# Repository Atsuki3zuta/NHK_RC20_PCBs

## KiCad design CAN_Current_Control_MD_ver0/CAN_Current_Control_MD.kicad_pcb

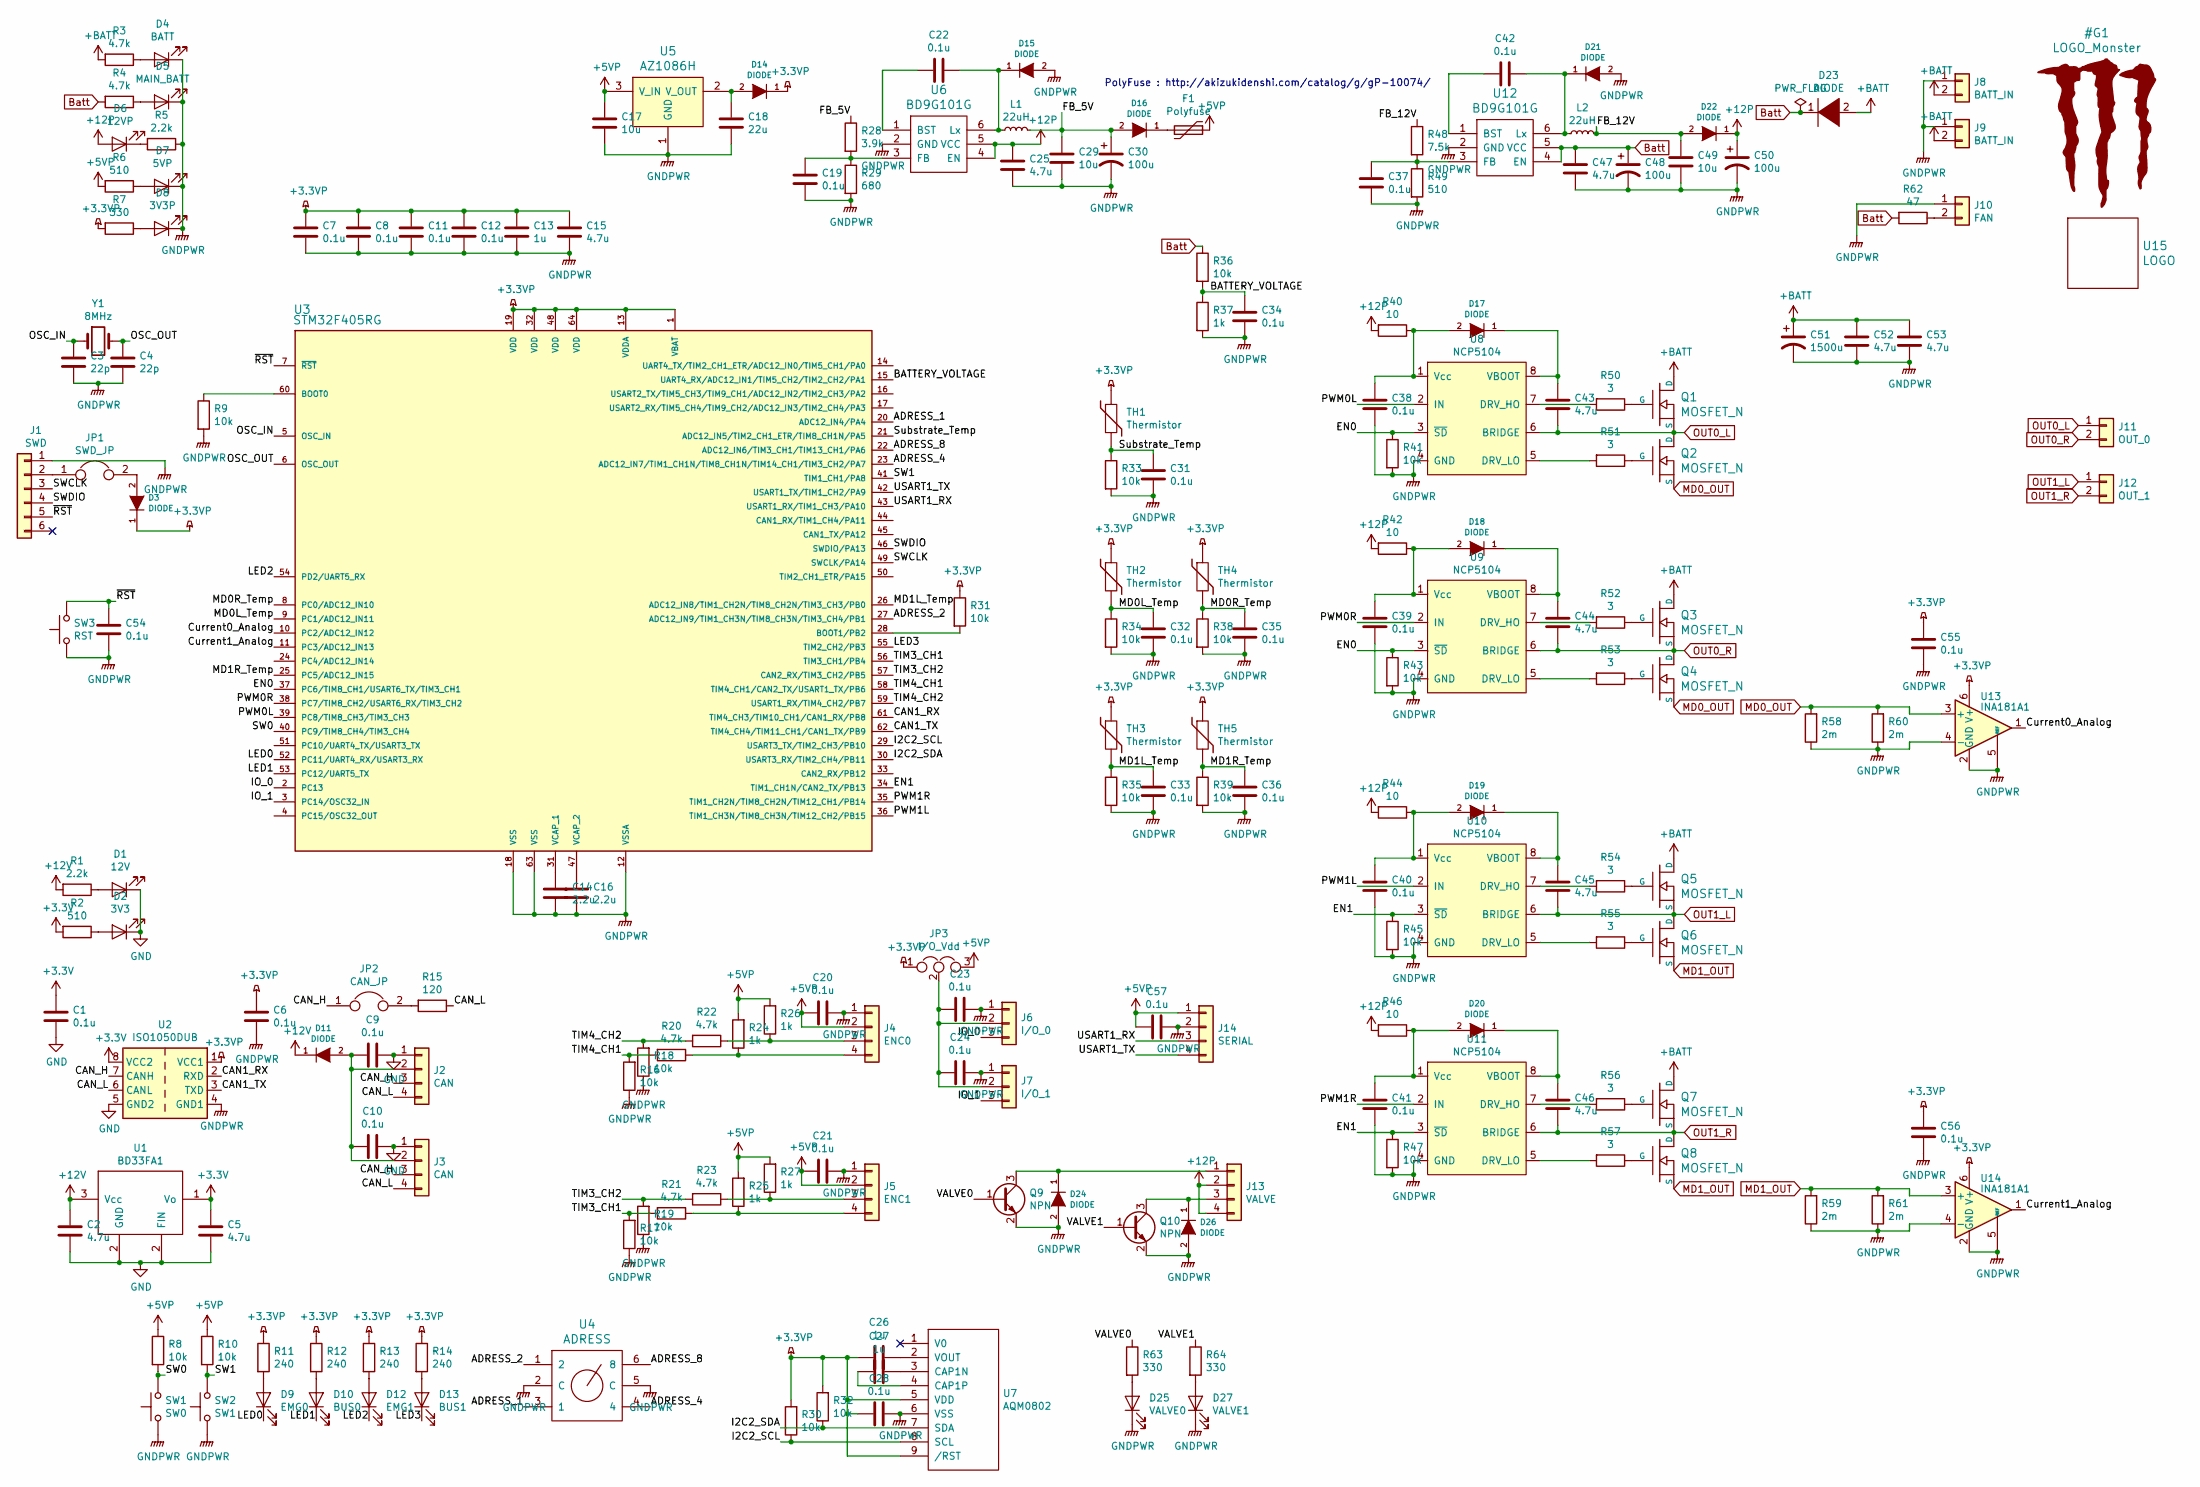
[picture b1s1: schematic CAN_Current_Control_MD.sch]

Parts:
C1, C8, C11, C12, C19, C20, C21, C22, C23, C24, C28, C31, C32, C33, C34, C35, C36, C38, C39, C40, C41, C42, C55, C56, C57: 0.1u; 1608_WP
C2, C5, C25, C43, C44, C45, C46, C47, C52, C53: 4.7u; C_0805_2012Metric
C3, C4: 22p; 1608_WP
C6, C7, C9, C10, C37, C54: 0.1u; C_0603_1608Metric
C13, C26, C27: 1u; 1608_WP
C14, C16: 2.2u; 1608_WP
C15: 4.7u; 1608_WP
C17: 10u; 1608_WP
C18: 22u; 1608_WP
C29, C49: 10u; C_0805_2012Metric
C30, C48, C50: 100u; CP_Radial_D5.0mm_P2.50mm
C51: 1500u; C_Radial_D13mm_H25.0mm_P5.00mm
D1: 12V; 1608_WP
D2: 3V3; 1608_WP
D3, D11, D14, D15, D16, D17, D18, D19, D20, D21, D22, D24, D26: DIODE; D_SOD-123
D4: BATT; LED_0603_1608Metric
D5: MAIN_BATT; LED_0603_1608Metric
D6: 12VP; LED_0603_1608Metric
D7: 5VP; LED_0603_1608Metric
D8: 3V3P; LED_0603_1608Metric
D9: EMG0; 1608_WP
D10: BUS0; 1608_WP
D12: EMG1; 1608_WP
D13: BUS1; 1608_WP
D23: DIODE; D_SMA
D25: VALVE0; LED_0603_1608Metric
D27: VALVE1; LED_0603_1608Metric
F1: Polyfuse; Fuse_1812_4532Metric_Pad1.30x3.40mm_HandSolder
J1: SWD; ZH_6P
J2, J3: CAN; XA_4L
J4: ENC0; XA_4L
J5: ENC1; XA_4L
J6: I/O_0; XA_3L
J7: I/O_1; XA_3L
J8: BATT_IN; XT60_F
J9: BATT_IN; XT60_M
J10: FAN; XA_2P
J11: OUT_0; XT60_F
J12: OUT_1; XT60_F
J13: VALVE; XA_4L
J14: SERIAL; PinSocket_1x04_P2.54mm_Vertical
JP1: SWD_JP; SolderJumper-2_P1.3mm_Open_TrianglePad1.0x1.5mm
JP2: CAN_JP; PinHeader_1x02_P2.54mm_Vertical
JP3: I/O_Vdd; PinHeader_1x03_P2.54mm_Vertical
L1, L2: 22uH; Inductor_Taiyo-Yuden_NR-50xx_HandSoldering
Q1, Q2, Q3, Q4, Q5, Q6, Q7, Q8: MOSFET_N; D2-PAK_compact
Q9, Q10: NPN; SOT-23
R1: 2.2k; 1608_WP
R2, R6: 510; 1608_WP
R3, R4: 4.7k; R_0603_1608Metric
R5: 2.2k; R_0603_1608Metric
R7, R63, R64: 330; 1608_WP
R8, R9, R10, R31: 10k; R_0603_1608Metric
R11, R12, R13, R14: 240; R_0603_1608Metric
R15: 120; R_0603_1608Metric
R16, R17, R18, R19, R30, R32, R33, R34, R35, R36, R38, R39, R41, R43, R45, R47: 10k; 1608_WP
R20, R21, R22, R23: 4.7k; 1608_WP
R24, R25, R26, R27, R37: 1k; 1608_WP
R28: 3.9k; R_0603_1608Metric
R29: 680; R_0603_1608Metric
R40, R42, R44, R46: 10; 1608_WP
R48: 7.5k; R_0603_1608Metric
R49: 510; R_0603_1608Metric
R50, R51, R52, R53, R54, R55, R56, R57: 3; R_0603_1608Metric
R58, R59, R60, R61: 2m; R_2010_5025Metric
R62: 47; R_2812
SW1: SW0; SW_SPST_PTS810
SW2: SW1; SW_SPST_PTS810
SW3: RST; SW_SPST_CK_RS282G05A3
TH1, TH2, TH3, TH4, TH5: Thermistor; 1608_WP
U1: BD33FA1; SOT-89-3
U2: ISO1050DUB; SOP-8_6.62x9.15mm_P2.54mm
U3: STM32F405RG; LQFP-64_10x10mm_P0.5mm
U4: ADRESS; rotary_0F
U5: AZ1086H; SOT-223-3_TabPin2
U6, U12: BD9G101G; TSOP-6_1.65x3.05mm_P0.95mm
U7: AQM0802; AQM0802_original
U8, U9, U10, U11: NCP5104; SOIC-8_3.9x4.9mm_P1.27mm
U13, U14: INA181A1; SOT-23-6
U15: LOGO; Mini_Monster
Y1: 8MHz; Crystal_SMD_5032_2Pads

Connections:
+3.3VP: C6.1, C7.1, C8.1, C11.1, C12.1, C13.1, C15.1, C26.2, C28.2, C55.1, C56.1, D3.1 (K), D14.1 (K), JP3.1, R7.2, R11.1, R12.1, R13.1, R14.1, R30.2, R31.1, R32.2, TH1.1, TH2.1, TH3.1, TH4.1, TH5.1, U2.1 (VCC1), U3.1 (VBAT), U3.13 (VDDA), U3.19 (VDD), U3.32 (VDD), U3.48 (VDD), U3.64 (VDD), U7.5 (VDD), U7.9 (/RST), U13.6 (V+), U14.6 (V+)
+3V3: C1.1, C5.1, R2.2, U1.1 (Vo), U2.8 (VCC2)
+5VP: C17.1, C20.2, C21.2, C57.2, F1.1, J4.2, J5.2, J14.1, JP3.3, R6.2, R8.1, R10.1, R24.2, R25.2, R26.2, R27.2, U5.3 (V_IN)
+12P: C25.1, C50.1, D6.2 (A), D22.1 (K), J13.2, J13.4, R40.2, R42.2, R44.2, R46.2, U6.4 (EN), U6.5 (VCC)
+12V: C2.1, D11.1 (K), R1.2, U1.3 (Vcc)
+BATT: C51.1, C52.1, C53.1, D23.2 (A), J8.2, J9.2, Q1.D, Q3.D, Q5.D, Q7.D, R3.2
/ADRESS_1: U3.20 (ADC12_IN4/PA4), U4.3 (1)
/ADRESS_2: U3.27 (ADC12_IN9/TIM1_CH3N/TIM8_CH3N/TIM3_CH4/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), U4.1 (2)
/ADRESS_4: U3.23 (ADC12_IN7/TIM1_CH1N/TIM8_CH1N/TIM14_CH1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), U4.4
/ADRESS_8: U3.22 (ADC12_IN6/TIM3_CH1/TIM13_CH1/PA6), U4.6 (8)
/BATTERY_VOLTAGE: C34.1, R36.2, R37.1, U3.15 (UART4_RX/ADC12_IN1/TIM5_CH2/TIM2_CH2/PA1)
/CAN1_RX: U2.2 (RXD), U3.61 (TIM4_CH3/TIM10_CH1/CAN1_RX/PB8)
/CAN1_TX: U2.3 (TXD), U3.62 (TIM4_CH4/TIM11_CH1/CAN1_TX/PB9)
/CAN_H: J2.3, J3.3, JP2.1, U2.7 (CANH)
/CAN_L: J2.4, J3.4, R15.1, U2.6 (CANL)
/Current0_Analog: U3.10 (PC2/ADC12_IN12), U13.1
/Current1_Analog: U3.11 (PC3/ADC12_IN13), U14.1
/EN0: R41.1, R43.1, U3.37 (PC6/TIM8_CH1/USART6_TX/TIM3_CH1), U8.3 (~SD), U9.3 (~SD)
/EN1: R45.1, R47.1, U3.34 (TIM1_CH1N/CAN2_TX/PB13), U10.3 (~SD), U11.3 (~SD)
/FB_5V: C29.1, C30.1, D16.2 (A), L1.2, R28.1
/FB_12V: C49.1, D22.2 (A), L2.2, R48.1
/I2C2_SCL: R30.1, U3.29 (USART3_TX/TIM2_CH3/PB10), U7.8 (SCL)
/I2C2_SDA: R32.1, U3.30 (USART3_RX/TIM2_CH4/PB11), U7.7 (SDA)
/IO_0: J6.3, U3.2 (PC13)
/IO_1: J7.3, U3.3 (PC14/OSC32_IN)
/LED0: D9.1 (K), U3.52 (PC11/UART4_RX/USART3_RX)
/LED1: D10.1 (K), U3.53 (PC12/UART5_TX)
/LED2: D12.1 (K), U3.54 (PD2/UART5_RX)
/LED3: D13.1 (K), U3.55 (TIM2_CH2/PB3)
/MD0L_Temp: C32.1, R34.1, TH2.2, U3.9 (PC1/ADC12_IN11)
/MD0R_Temp: C35.1, R38.1, TH4.2, U3.8 (PC0/ADC12_IN10)
/MD1L_Temp: C33.1, R35.1, TH3.2, U3.26 (ADC12_IN8/TIM1_CH2N/TIM8_CH2N/TIM3_CH3/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)
/MD1R_Temp: C36.1, R39.1, TH5.2, U3.25 (PC5/ADC12_IN15)
/OSC_IN: C3.1, U3.5 (OSC_IN), Y1.1
/OSC_OUT: C4.1, U3.6 (OSC_OUT), Y1.2
/PWM0L: U3.39 (PC8/TIM8_CH3/TIM3_CH3), U8.2 (IN)
/PWM0R: U3.38 (PC7/TIM8_CH2/USART6_RX/TIM3_CH2), U9.2 (IN)
/PWM1L: U3.36 (TIM1_CH3N/TIM8_CH3N/TIM12_CH2/PB15), U10.2 (IN)
/PWM1R: U3.35 (TIM1_CH2N/TIM8_CH2N/TIM12_CH1/PB14), U11.2 (IN)
/SW0: R8.2, SW1.2, U3.40 (PC9/TIM8_CH4/TIM3_CH4)
/SW1: R10.2, SW2.2, U3.41 (TIM1_CH1/PA8)
/SWCLK: J1.3, U3.49 (SWCLK/PA14)
/SWDIO: J1.4, U3.46 (SWDIO/PA13)
/Substrate_Temp: C31.1, R33.1, TH1.2, U3.21 (ADC12_IN5/TIM2_CH1_ETR/TIM8_CH1N/PA5)
/TIM3_CH1: R17.2, R21.2, U3.56 (TIM3_CH1/PB4)
/TIM3_CH2: R19.2, R23.2, U3.57 (CAN2_RX/TIM3_CH2/PB5)
/TIM4_CH1: R16.2, R20.2, U3.58 (TIM4_CH1/CAN2_TX/USART1_TX/PB6)
/TIM4_CH2: R18.2, R22.2, U3.59 (USART1_RX/TIM4_CH2/PB7)
/USART1_RX: J14.3, U3.43 (USART1_RX/TIM1_CH3/PA10)
/USART1_TX: J14.4, U3.42 (USART1_TX/TIM1_CH2/PA9)
/VALVE0: Q9.1 (B), R63.1
/VALVE1: Q10.1 (B), R64.1
/~RST: C54.1, J1.5, SW3.2, U3.7 (~RST)
Batt: C47.1, C48.1, D23.1 (K), R4.2, R36.1, R62.2, U12.4 (EN), U12.5 (VCC)
GND: C1.2, C2.2, C5.2, C9.1, C10.1, D1.1 (K), D2.1 (K), J2.1, J3.1, U1.2 (FIN), U2.5 (GND2)
GNDPWR: C3.2, C4.2, C6.2, C7.2, C8.2, C11.2, C12.2, C13.2, C14.2, C15.2, C16.2, C17.2, C18.2, C19.2, C20.1, C21.1, C23.1, C24.1, C25.2, C28.1, C29.2, C30.2, C31.2, C32.2, C33.2, C34.2, C35.2, C36.2, C37.2, C38.2, C39.2, C40.2, C41.2, C47.2, C48.2, C49.2, C50.2, C51.2, C52.2, C53.2, C54.2, C55.2, C56.2, C57.1, D4.1 (K), D5.1 (K), D7.1 (K), D8.1 (K), D15.2 (A), D21.2 (A), D24.2 (A), D25.1 (K), D26.2 (A), D27.1 (K), J1.1, J4.1, J5.1, J6.1, J7.1, J8.1, J9.1, J10.1, J14.2, Q9.2 (E), Q10.2 (E), R5.1, R9.2, R16.1, R17.1, R18.1, R19.1, R29.2, R33.2, R34.2, R35.2, R37.2, R38.2, R39.2, R41.2, R43.2, R45.2, R47.2, R49.2, R58.1, R59.1, R60.1, R61.1, SW1.1, SW2.1, SW3.1, U2.4 (GND1), U3.12 (VSSA), U3.18 (VSS), U3.63 (VSS), U4.2 (C), U4.5 (C), U5.1 (GND), U6.2 (GND), U7.6 (VSS), U8.4 (GND), U9.4 (GND), U10.4 (GND), U11.4 (GND), U12.2 (GND), U13.2 (GND), U13.4 (-), U13.5 (REF), U14.2 (GND), U14.4 (-), U14.5 (REF)
MD0_OUT: Q2.S, Q4.S, R58.2, R60.2, U13.3 (+)
MD1_OUT: Q6.S, Q8.S, R59.2, R61.2, U14.3 (+)
unnamed: C9.2, C10.2, D11.2 (A), J2.2, J3.2
unnamed: C14.1, U3.31 (VCAP_1)
unnamed: C16.1, U3.47 (VCAP_2)
unnamed: C18.1, D14.2 (A), U5.2 (V_OUT)
unnamed: C19.1, R28.2, R29.1, U6.3 (FB)
unnamed: C22.1, D15.1 (K), L1.1, U6.6 (Lx)
unnamed: C22.2, U6.1 (BST)
unnamed: C23.2, C24.2, J6.2, J7.2, JP3.2
unnamed: C26.1, U7.2 (VOUT)
unnamed: C27.1, U7.3 (CAP1N)
unnamed: C27.2, U7.4 (CAP1P)
unnamed: C37.1, R48.2, R49.1, U12.3 (FB)
unnamed: C38.1, D17.2 (A), R40.1, U8.1 (Vcc)
unnamed: C39.1, D18.2 (A), R42.1, U9.1 (Vcc)
unnamed: C40.1, D19.2 (A), R44.1, U10.1 (Vcc)
unnamed: C41.1, D20.2 (A), R46.1, U11.1 (Vcc)
unnamed: C42.1, D21.1 (K), L2.1, U12.6 (Lx)
unnamed: C42.2, U12.1 (BST)
unnamed: C43.1, D17.1 (K), U8.8 (VBOOT)
unnamed: C44.1, D18.1 (K), U9.8 (VBOOT)
unnamed: C45.1, D19.1 (K), U10.8 (VBOOT)
unnamed: C46.1, D20.1 (K), U11.8 (VBOOT)
unnamed: D1.2 (A), R1.1
unnamed: D2.2 (A), R2.1
unnamed: D3.2 (A), JP1.2
unnamed: D4.2 (A), R3.1
unnamed: D5.2 (A), R4.1
unnamed: D6.1 (K), R5.2
unnamed: D7.2 (A), R6.1
unnamed: D8.2 (A), R7.1
unnamed: D9.2 (A), R11.2
unnamed: D10.2 (A), R12.2
unnamed: D12.2 (A), R13.2
unnamed: D13.2 (A), R14.2
unnamed: D16.1 (K), F1.2
unnamed: D24.1 (K), J13.1, Q9.3 (C)
unnamed: D25.2 (A), R63.2
unnamed: D26.1 (K), J13.3, Q10.3 (C)
unnamed: D27.2 (A), R64.2
unnamed: J1.2, JP1.1
unnamed: J4.3, R22.1, R26.1
unnamed: J4.4, R20.1, R24.1
unnamed: J5.3, R23.1, R27.1
unnamed: J5.4, R21.1, R25.1
unnamed: J10.2, R62.1
unnamed: JP2.2, R15.2
unnamed: Q1.G, R50.1
unnamed: Q2.G, R51.1
unnamed: Q3.G, R52.1
unnamed: Q4.G, R53.1
unnamed: Q5.G, R54.1
unnamed: Q6.G, R55.1
unnamed: Q7.G, R56.1
unnamed: Q8.G, R57.1
unnamed: R9.1, U3.60 (BOOT0)
unnamed: R31.2, U3.28 (BOOT1/PB2)
unnamed: R50.2, U8.7 (DRV_HO)
unnamed: R51.2, U8.5 (DRV_LO)
unnamed: R52.2, U9.7 (DRV_HO)
unnamed: R53.2, U9.5 (DRV_LO)
unnamed: R54.2, U10.7 (DRV_HO)
unnamed: R55.2, U10.5 (DRV_LO)
unnamed: R56.2, U11.7 (DRV_HO)
unnamed: R57.2, U11.5 (DRV_LO)
OUT0_L: C43.2, J11.1, Q1.S, Q2.D, U8.6 (BRIDGE)
OUT0_R: C44.2, J11.2, Q3.S, Q4.D, U9.6 (BRIDGE)
OUT1_L: C45.2, J12.1, Q5.S, Q6.D, U10.6 (BRIDGE)
OUT1_R: C46.2, J12.2, Q7.S, Q8.D, U11.6 (BRIDGE)

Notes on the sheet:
PolyFuse : http://akizukidenshi.com/catalog/g/gP-10074/

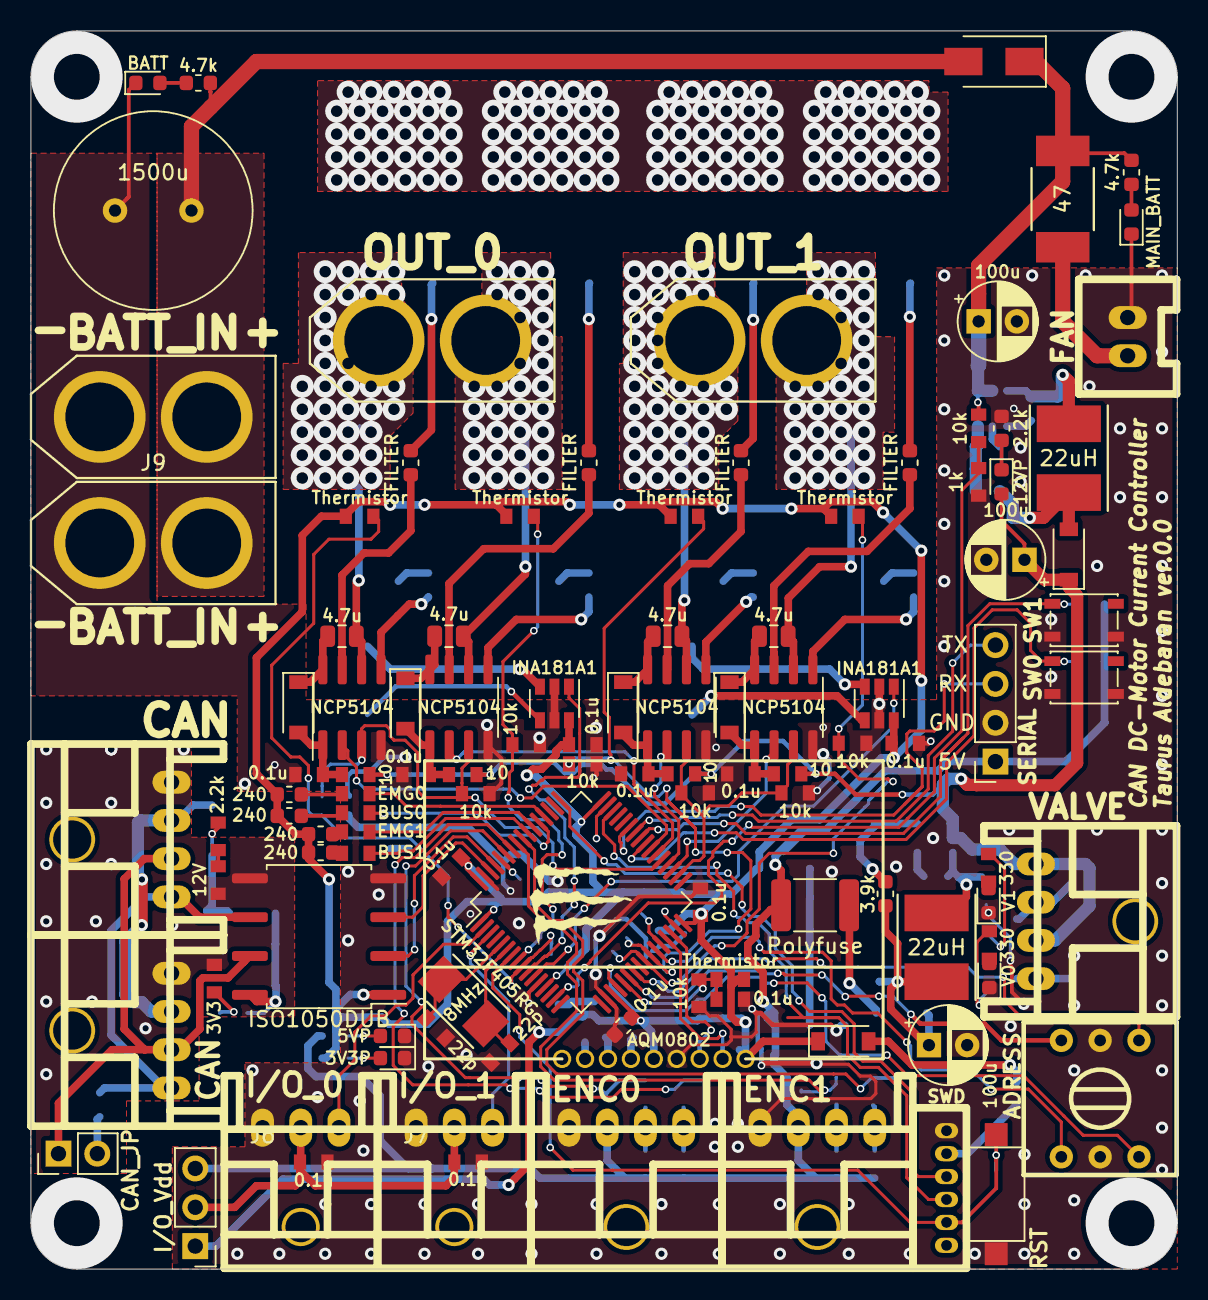
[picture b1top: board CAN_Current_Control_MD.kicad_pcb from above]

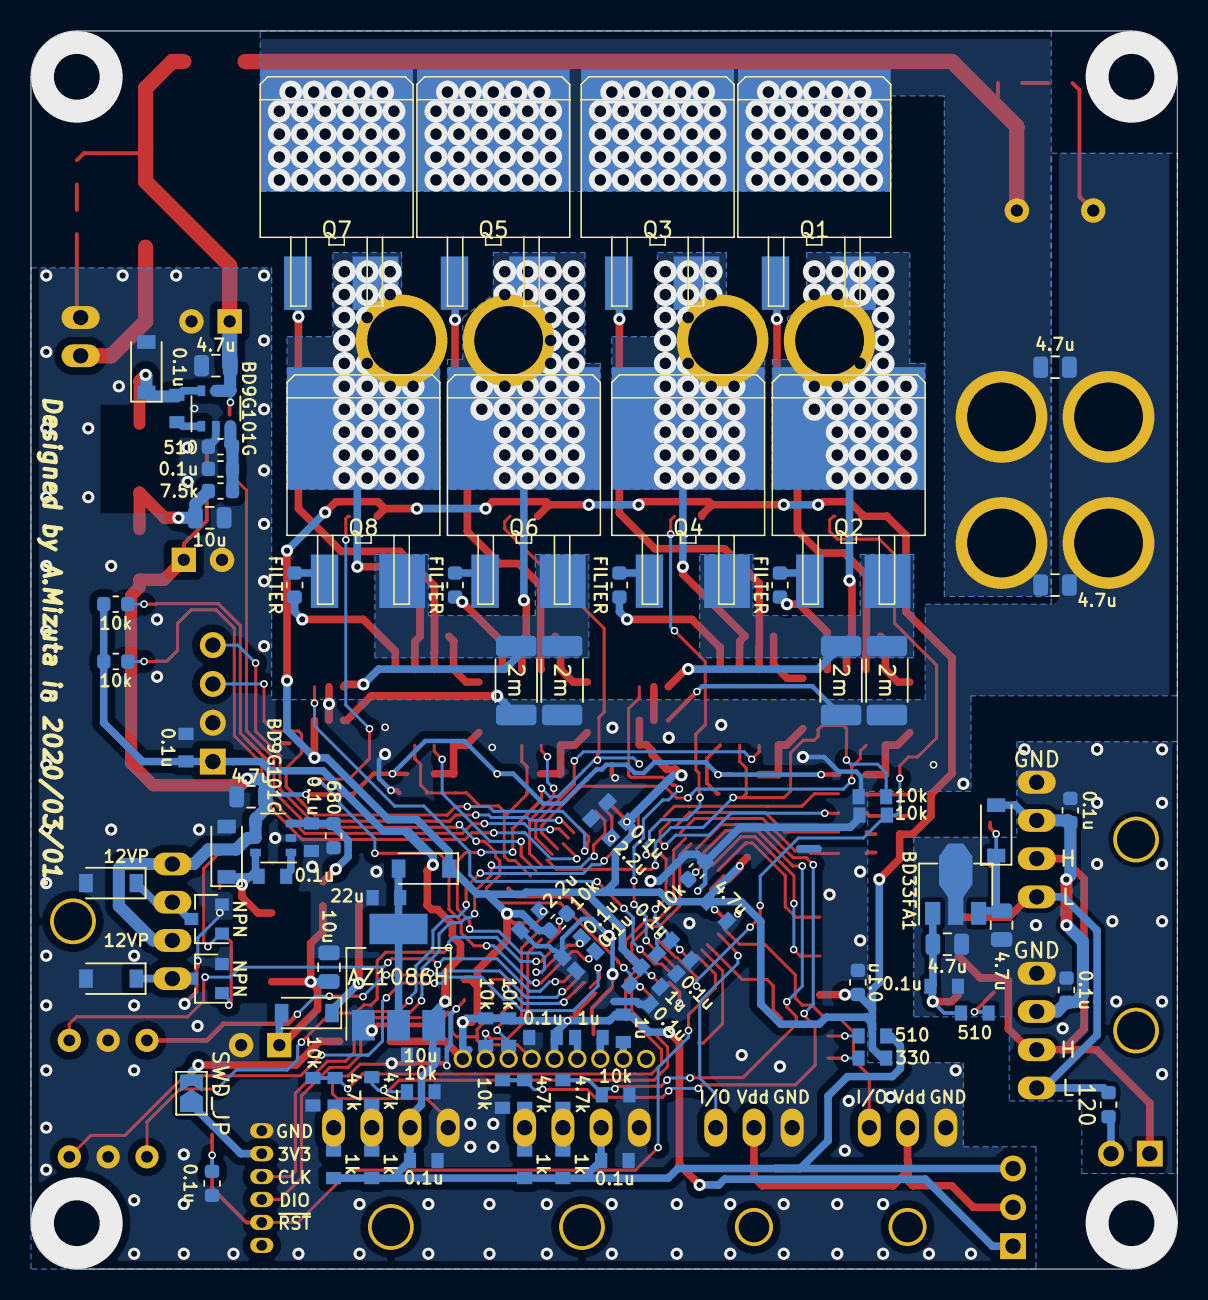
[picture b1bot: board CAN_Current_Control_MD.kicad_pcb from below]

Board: 2 copper layers, 75.0 x 81.0 mm, 202 parts (92 on the bottom side), 126 nets.

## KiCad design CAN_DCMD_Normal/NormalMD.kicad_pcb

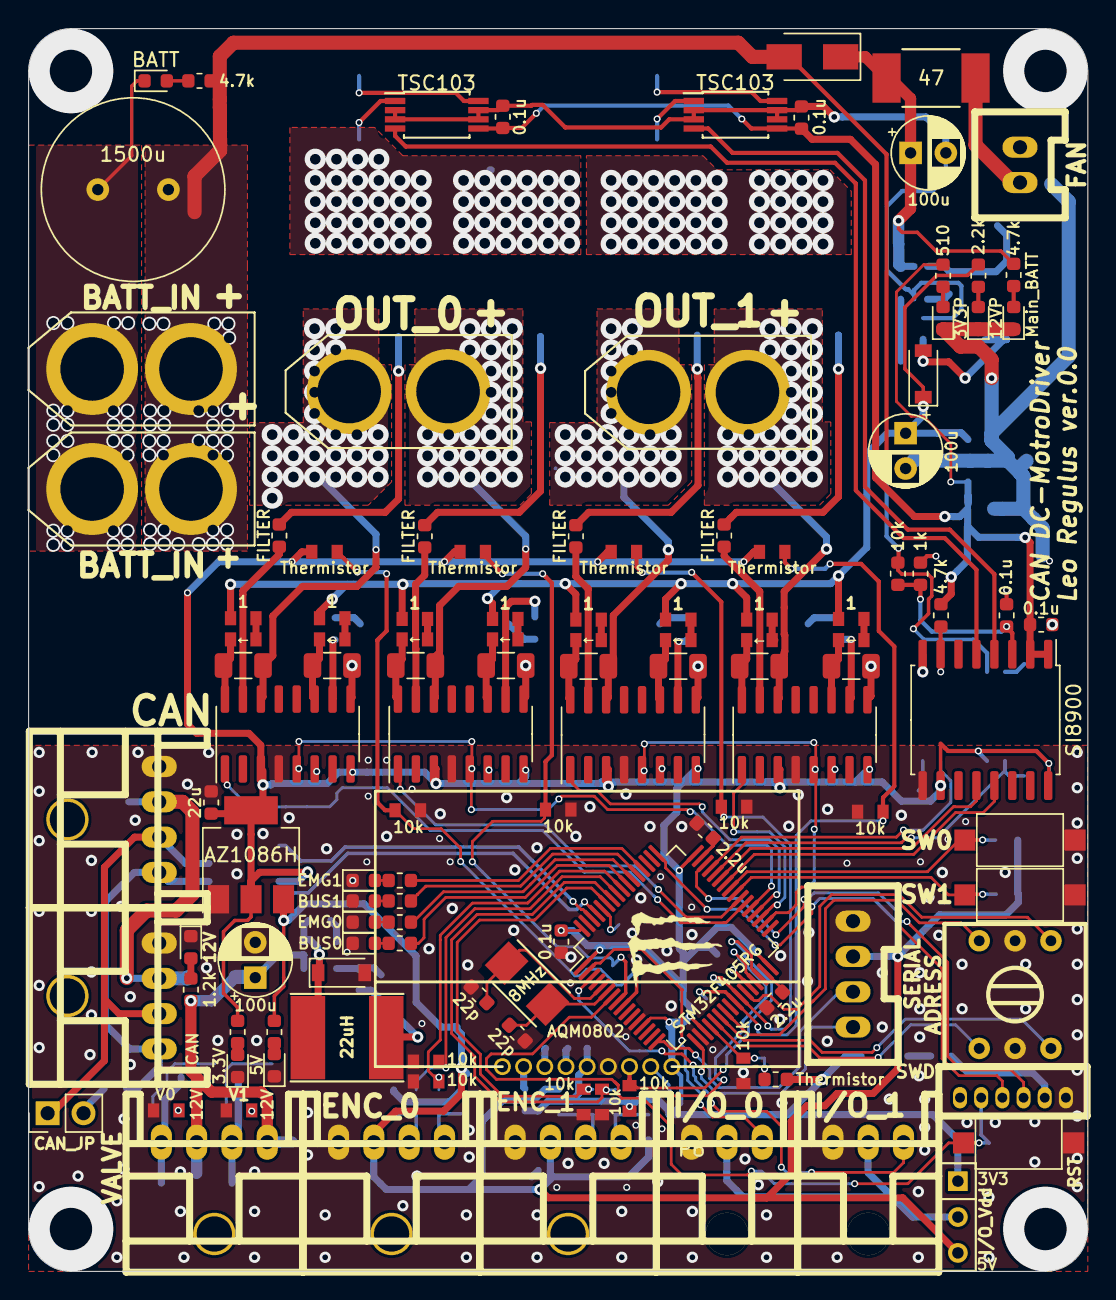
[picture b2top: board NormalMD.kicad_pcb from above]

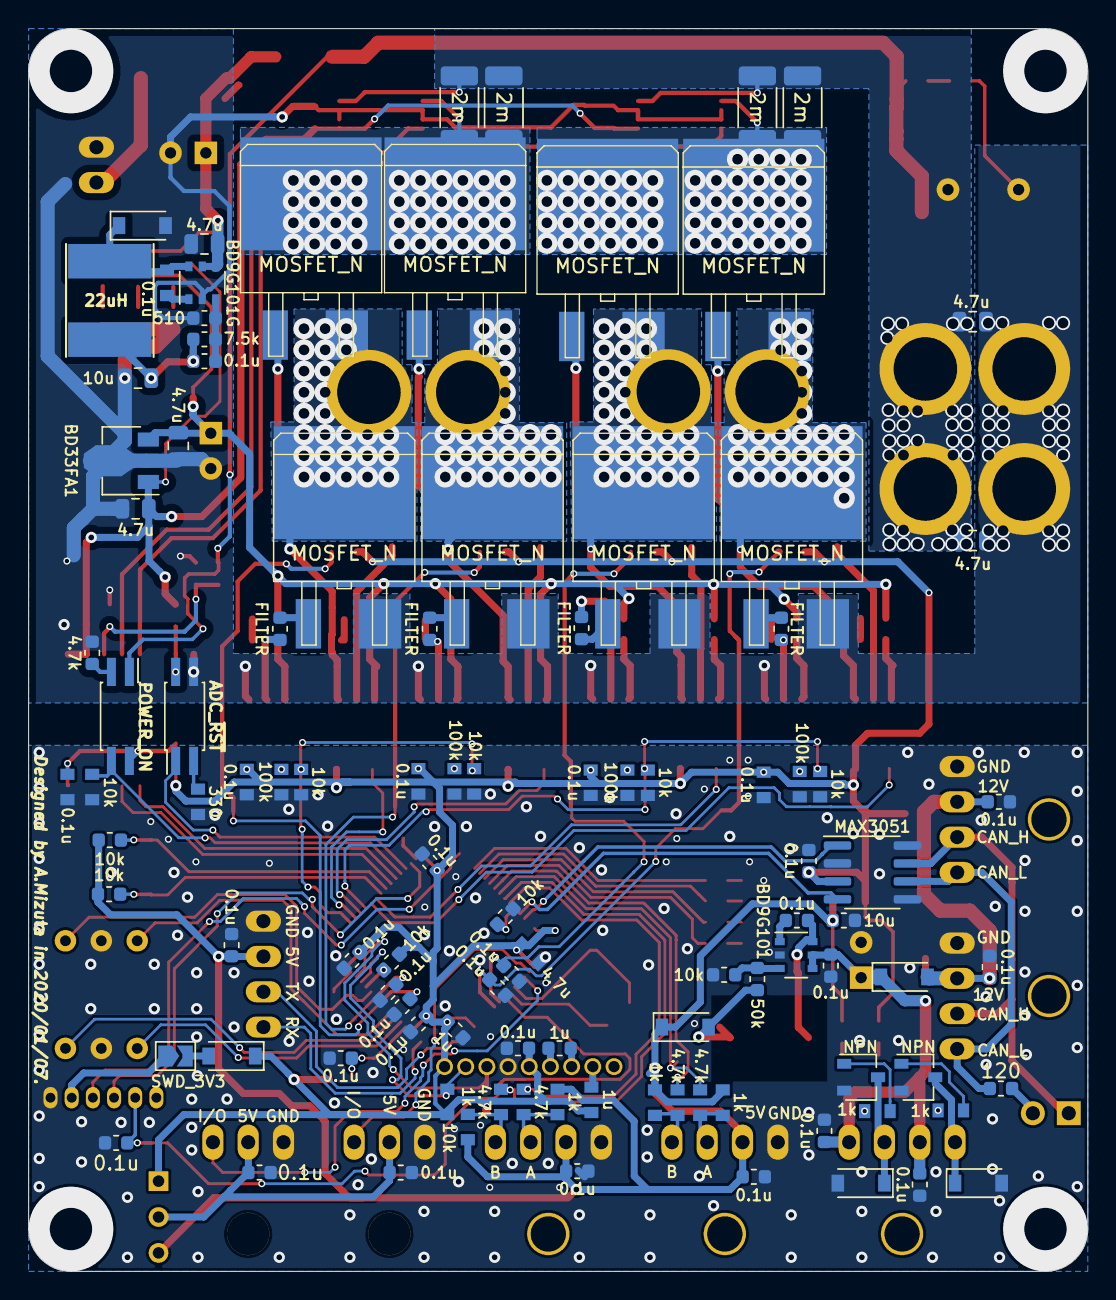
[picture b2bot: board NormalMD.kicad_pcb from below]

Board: 2 copper layers, 75.0 x 88.0 mm, 224 parts (103 on the bottom side), 143 nets.

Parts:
AMP1, AMP2: TSC103; TSSOP-8_4.4x3mm_P0.65mm
C1, C3: 22p; C_0603_1608Metric
C2, C5, C6, C7, C8, C9, C11, C15, C16, C18, C21, C22, C24, C26, C27, C36, C38, C39, C42, C44, C51, C53, C54, C55, C58, C59, C60, C61: 0.1u; C_0603_1608Metric
C4, C17, C23, C40, C41, C52: 0.1u; 1608_WP
C10, C63: 1u; C_0603_1608Metric
C12: 4.7u; 1608_WP
C13, C14: 2.2u; C_0603_1608Metric
C19, C20, C30, C31, C45, C46, C48, C49: 4.7u; C_1206_3216Metric
C25, C33, C64: 100u; CP_Radial_D5.0mm_P2.50mm
C28: 10u; C_0805_2012Metric
C29, C32, C35, C37, C43: 4.7u; C_0805_2012Metric
C34: 1500u; C_Radial_D13.0mm_H25.0mm_P5.00mm
C56: 10u; C_0603_1608Metric
C57: 22u; C_0603_1608Metric
C62: 1u; 1608_WP
D1, D2, D3, D11, D13, D14, D19, D20: DIODE; 1608_WP
D4, D5, D6, D10, D16, D18, D24, D26: DIODE; D_SOD-123
D7: EMG1; LED_0603_1608Metric
D8: BUS1; LED_0603_1608Metric
D9: EMG0; LED_0603_1608Metric
D12: VALVE0; 1608_WP
D15: DIODE; D_SMA
D17: VALVE1; 1608_WP
D21: BATT; LED_0603_1608Metric
D22: 12VP; LED_0603_1608Metric
D23: 3V3P; LED_0603_1608Metric
D27: Main_BATT; LED_0603_1608Metric
D32: 12V; LED_0603_1608Metric
D33: 5V; LED_0603_1608Metric
D34: 3.3V; LED_0603_1608Metric
D39: BUS0; LED_0603_1608Metric
JP1: SWD_3V3; SolderJumper-2_P1.3mm_Open_TrianglePad1.0x1.5mm
JP2: CAN_JP; PinHeader_1x02_P2.54mm_Vertical
JP3: I/O_Vdd; SW_Micro_SPST
L1, L2: 22uH; Inductor_Taiyo-Yuden_NR-60xx_HandSoldering
P1: SWD; ZH_6P
P2: VALVE; XA_4L
P3, P4: CAN; XA_4L
P5: SERIAL; XA_4P
P6: I/O_0; XA_3LC
P7: FAN; XA_2P
P8: BATT_IN; XT60_M
P9: BATT_IN; XT60_F
P10: OUT_1; XT60_F
P11: ENC_0; XA_4L
P13: ENC_1; XA_4L
P14: I/O_1; XA_3LC
P15: OUT_0; XT60_F
Q1, Q2, Q3, Q4, Q5, Q6, Q7, Q8: MOSFET_N; D2-PAK_compact
Q9, Q10: NPN; SOT-23W
R1, R4, R5, R9, R22, R38: 10k; R_0603_1608Metric
R2, R10, R26, R27, R36, R39, R52, R61, R62, R66, R67, R68, R69, R70, R73, R74: 10k; 1608_WP
R3: 120; R_0603_1608Metric
R6, R7, R8, R49, R51: 330; R_0603_1608Metric
R11, R13, R35, R65: 100k; 1608_WP
R12: 330; 1608_WP
R14: 7.5k; R_0603_1608Metric
R15, R34, R48: 510; R_0603_1608Metric
R16, R32, R40, R41: 4.7k; R_0603_1608Metric
R17, R18, R30, R31, R53, R54, R63, R64: FILTER; R_0603_1608Metric
R19, R20, R28, R29, R55, R56, R58, R59: 1; 1608_WP
R21, R24, R42, R43, R71, R72: 1k; 1608_WP
R23: 1k; R_0603_1608Metric
R25: 47; R_2812
R33: 2.2k; R_0603_1608Metric
R37: 50k; R_0603_1608Metric
R44, R45, R46, R50: 4.7k; 1608_WP
R47: 1.2k; R_0603_1608Metric
R57, R60, R75, R76: 2m; R_2010_5025Metric
SW1: RST; SW_SPST_CK_RS282G05A3
SW3: SW0; SW_SPST_CK_RS282G05A3
SW4: SW1; SW_SPST_CK_RS282G05A3
TH1, TH2, TH3, TH4: Thermistor; 1608_WP
TH5: Thermistor; C_0603_1608Metric
U1: MAX3051; SOIC-8_3.9x4.9mm_P1.27mm
U2: BD9G101; TSOP-6_1.65x3.05mm_P0.95mm
U3: STM32F405RG; LQFP-64_10x10mm_P0.5mm
U4, U8, U12, U14: SI8274; SOIC-16_3.9x9.9mm_P1.27mm
U5: SI8900; SOIC-16W_7.5x10.3mm_P1.27mm
U6: ADC_~RST; SO-4_4.4x2.3mm_P1.27mm
U7: BD9G101G; TSOP-6_1.65x3.05mm_P0.95mm
U9: BD33FA1; SOT-89-3
U11: POWER_ON; SO-4_4.4x2.3mm_P1.27mm
U15: AZ1086H; SOT-223-3_TabPin2
U16: LOGO; Mini_Monster
U17: AQM0802; AQM0802_original
U19: ADRESS; rotary_0F
Y1: 8MHz; Crystal_SMD_5032_2Pads

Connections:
+3.3VP: AMP1.5, AMP2.5, C21.1, C22.1, C32.1, C36.1, R16.1, R34.2, U5.1, U5.2, U9.1
+3V3: C4.1, C5.1, C6.1, C8.1, C9.1, C10.1, C12.1, C17.1, C40.1, C41.1, C42.1, C52.1, C57.1, C61.2, C62.2, D4.1, JP3.1, R9.1, R49.2, R73.1, R74.1, TH1.1, TH2.1, TH3.1, TH4.1, TH5.1, U1.3, U3.1, U3.13, U3.19, U3.32, U3.48, U3.64, U4.3, U4.8, U5.10, U5.16, U8.3, U8.8, U11.4, U12.3, U12.8, U14.3, U14.8, U15.2, U17.5, U17.9
+5V: C15.2, C26.2, C44.2, C56.1, D26.1, JP3.3, P5.2, P11.2, P13.2, R4.1, R5.1, R21.1, R24.1, R42.1, R43.1, R48.2, U15.3
+12P: C29.1, C64.1, D18.1, R19.1, R20.1, R28.1, R29.1, R33.2, R55.1, R56.1, R58.1, R59.1, U9.3
+12V: C27.1, C33.1, C38.1, C51.1, D5.1, P2.2, P2.4, R47.2, U2.4, U2.5
+BATT: AMP1.8, AMP2.8, C34.1, C35.1, C43.1, D15.2, P8.2, P9.2, R22.1, R32.2, R57.1, R60.1, R75.1, R76.1, U11.1
/ADC_~RST: R16.2, U5.7, U6.4
/ADC_~RST~_PIN: U3.45, U6.1
/ADR_1: U3.23, U19.3
/ADR_2: U3.27, U19.1
/ADR_4: U3.21, U19.4
/ADR_8: U3.22, U19.6
/CAN1_RX: U1.4, U3.61
/CAN1_TX: U1.1, U3.62
/CAN_H: JP2.1, P3.3, P4.3, U1.7
/CAN_L: P3.4, P4.4, R3.1, U1.6
/CAN_Vdd: C7.2, C11.2, D5.2, P3.2, P4.2
/Current0: AMP1.4, U5.5
/Current1: AMP2.4, U5.4
/EN0: R10.1, R36.1, U3.37, U4.5, U12.5
/EN1: R2.1, R66.1, U3.34, U8.5, U14.5
/FB: R37.2, R38.1, U2.3
/FB_PWR: C18.2, R14.2, R15.1, U7.3
/FB_PWR_OUT: C18.1, C28.1, D18.2, L1.2, R14.1
/I2C2_SCL: R73.2, U3.29, U17.8
/I2C2_SDA: R74.2, U3.30, U17.7
/IO_0: P6.3, U3.2
/IO_1: P14.3, U3.3
/LED0: R6.1, U3.52
/LED1: R7.1, U3.53
/LED2: R8.1, U3.54
/LED3: R51.1, U3.55
/MOTOR0_BATT: AMP1.1, Q1.D, Q5.D, R57.2, R60.2
/MOTOR1_BATT: AMP2.1, Q3.D, Q7.D, R75.2, R76.2
/Motor0L_Tmp: C53.1, R67.1, TH1.2, U3.9
/Motor0R_Tmp: C58.1, R52.1, TH3.2, U3.8
/Motor1L_Tmp: C54.1, R68.1, TH2.2, U3.26
/Motor1R_Tmp: C59.1, R69.1, TH4.2, U3.25
/OSC_IN: C1.2, U3.5, Y1.1
/OSC_OUT: C3.2, U3.6, Y1.2
/OUT0_L: C19.2, P15.1, Q1.S, Q2.D, U4.14
/OUT0_R: C30.2, P15.2, Q5.S, Q6.D, U12.14
/OUT1_L: C45.2, P10.1, Q3.S, Q4.D, U8.14
/OUT1_R: C48.2, P10.2, Q7.S, Q8.D, U14.14
/PWM0_L: U3.38, U4.1
/PWM0_R: U3.39, U12.1
/PWM1_L: U3.36, U8.1
/PWM1_R: U3.35, U14.1
/PWR_ON_PIN: R39.1, U3.44, U11.3
/SW0: R4.2, SW3.2, U3.41
/SW1: R5.2, SW4.2, U3.40
/SWCLK: P1.3, U3.49
/SWDIO: P1.4, U3.46
/Substrate_Temp: C60.1, R70.1, TH5.2, U3.20
/TIM3_CH1: R26.1, R44.2, U3.56
/TIM3_CH2: R45.2, R61.1, U3.57
/TIM4_CH1: R27.1, R46.2, U3.58
/TIM4_CH2: R50.2, R62.1, U3.59
/USART1_RX: U3.43, U5.12
/USART1_TX: U3.42, U5.13
/USART2_RX: P5.4, U3.17
/USART2_TX: P5.3, U3.16
/VALVE0: Q9.1, R71.1
/VALVE1: Q10.1, R72.1
/Voltage: C24.1, R22.2, R23.1, U5.3
/batt: C25.1, C37.1, D15.1, R25.2, R41.2, U7.4, U7.5
/~RST: C2.2, P1.5, SW1.1, U3.7
GND: C1.1, C2.1, C3.1, C4.2, C5.2, C6.2, C7.1, C8.2, C9.2, C10.2, C11.1, C12.2, C13.2, C14.2, C15.1, C16.1, C17.2, C26.1, C27.2, C33.2, C38.2, C40.2, C41.2, C42.2, C44.1, C51.2, C52.2, C53.2, C54.2, C55.1, C56.2, C57.2, C58.2, C59.2, C60.2, C61.1, D6.2, D7.1, D8.1, D9.1, D10.2, D12.1, D17.1, D24.2, D32.1, D33.1, D34.1, D39.1, P1.1, P3.1, P4.1, P5.1, P6.1, P11.1, P13.1, P14.1, Q9.2, Q10.2, R1.2, R2.2, R10.2, R11.2, R12.2, R13.2, R26.2, R27.2, R35.2, R36.2, R38.2, R39.2, R52.2, R61.2, R62.2, R65.2, R66.2, R67.2, R68.2, R69.2, R70.2, SW1.2, SW3.1, SW4.1, U1.2, U1.5, U1.8, U2.2, U3.12, U3.18, U3.63, U4.4, U5.9, U8.4, U12.4, U14.4, U15.1, U17.6, U19.2, U19.5
GNDPWR: AMP1.2, AMP1.3, AMP1.6, AMP1.7, AMP2.2, AMP2.3, AMP2.6, AMP2.7, C20.2, C21.2, C22.2, C24.2, C25.2, C28.2, C29.2, C31.2, C32.2, C34.2, C35.2, C36.2, C37.2, C43.2, C46.2, C49.2, C64.2, D16.2, D21.1, D22.1, D23.1, D27.1, P7.1, P8.1, P9.1, Q2.S, Q4.S, Q6.S, Q8.S, R15.2, R23.2, R40.2, U4.9, U5.8, U6.3, U7.2, U8.9, U9.2, U12.9, U14.9
IO_Vdd: C16.2, C55.2, JP3.2, P6.2, P14.2
unnamed: C13.1, U3.31
unnamed: C14.1, U3.47
unnamed: C19.1, D13.1, U4.16
unnamed: C20.1, D14.1, U4.11
unnamed: C23.1, D16.1, L1.1, U7.6
unnamed: C23.2, U7.1
unnamed: C30.1, D19.1, U12.16
unnamed: C31.1, D20.1, U12.11
unnamed: C39.1, D24.1, L2.1, U2.6
unnamed: C39.2, U2.1
unnamed: C45.1, D1.1, U8.16
unnamed: C46.1, D2.1, U8.11
unnamed: C48.1, D3.1, U14.16
unnamed: C49.1, D11.1, U14.11
unnamed: C62.1, U17.2
unnamed: C63.1, U17.3
unnamed: C63.2, U17.4
unnamed: D1.2, R55.2
unnamed: D2.2, R56.2
unnamed: D3.2, R58.2
unnamed: D4.2, JP1.2
unnamed: D6.1, P2.1, Q9.3
unnamed: D7.2, R6.2
unnamed: D8.2, R7.2
unnamed: D9.2, R8.2
unnamed: D10.1, P2.3, Q10.3
unnamed: D11.2, R59.2
unnamed: D12.2, R71.2
unnamed: D13.2, R19.2
unnamed: D14.2, R20.2
unnamed: D17.2, R72.2
unnamed: D19.2, R28.2
unnamed: D20.2, R29.2
unnamed: D21.2, R32.1
unnamed: D22.2, R33.1
unnamed: D23.2, R34.1
unnamed: D26.2, L2.2, R37.1
unnamed: D27.2, R41.1
unnamed: D32.2, R47.1
unnamed: D33.2, R48.1
unnamed: D34.2, R49.1
unnamed: D39.2, R51.2
unnamed: JP1.1, P1.2
unnamed: JP2.2, R3.2
unnamed: P7.2, R25.1
unnamed: P11.3, R43.2, R45.1
unnamed: P11.4, R42.2, R44.1
unnamed: P13.3, R24.2, R50.1
unnamed: P13.4, R21.2, R46.1
unnamed: Q1.G, R17.1
unnamed: Q2.G, R18.1
unnamed: Q3.G, R53.1
unnamed: Q4.G, R54.1
unnamed: Q5.G, R30.1
unnamed: Q6.G, R31.1
unnamed: Q7.G, R63.1
unnamed: Q8.G, R64.1
unnamed: R1.1, U3.60
unnamed: R9.2, U3.28
unnamed: R11.1, U4.6
unnamed: R12.1, U6.2
unnamed: R13.1, U8.6
unnamed: R17.2, U4.15
unnamed: R18.2, U4.10
unnamed: R30.2, U12.15
unnamed: R31.2, U12.10
unnamed: R35.1, U12.6
unnamed: R40.1, U11.2
unnamed: R53.2, U8.15
unnamed: R54.2, U8.10
unnamed: R63.2, U14.15
unnamed: R64.2, U14.10
unnamed: R65.1, U14.6
